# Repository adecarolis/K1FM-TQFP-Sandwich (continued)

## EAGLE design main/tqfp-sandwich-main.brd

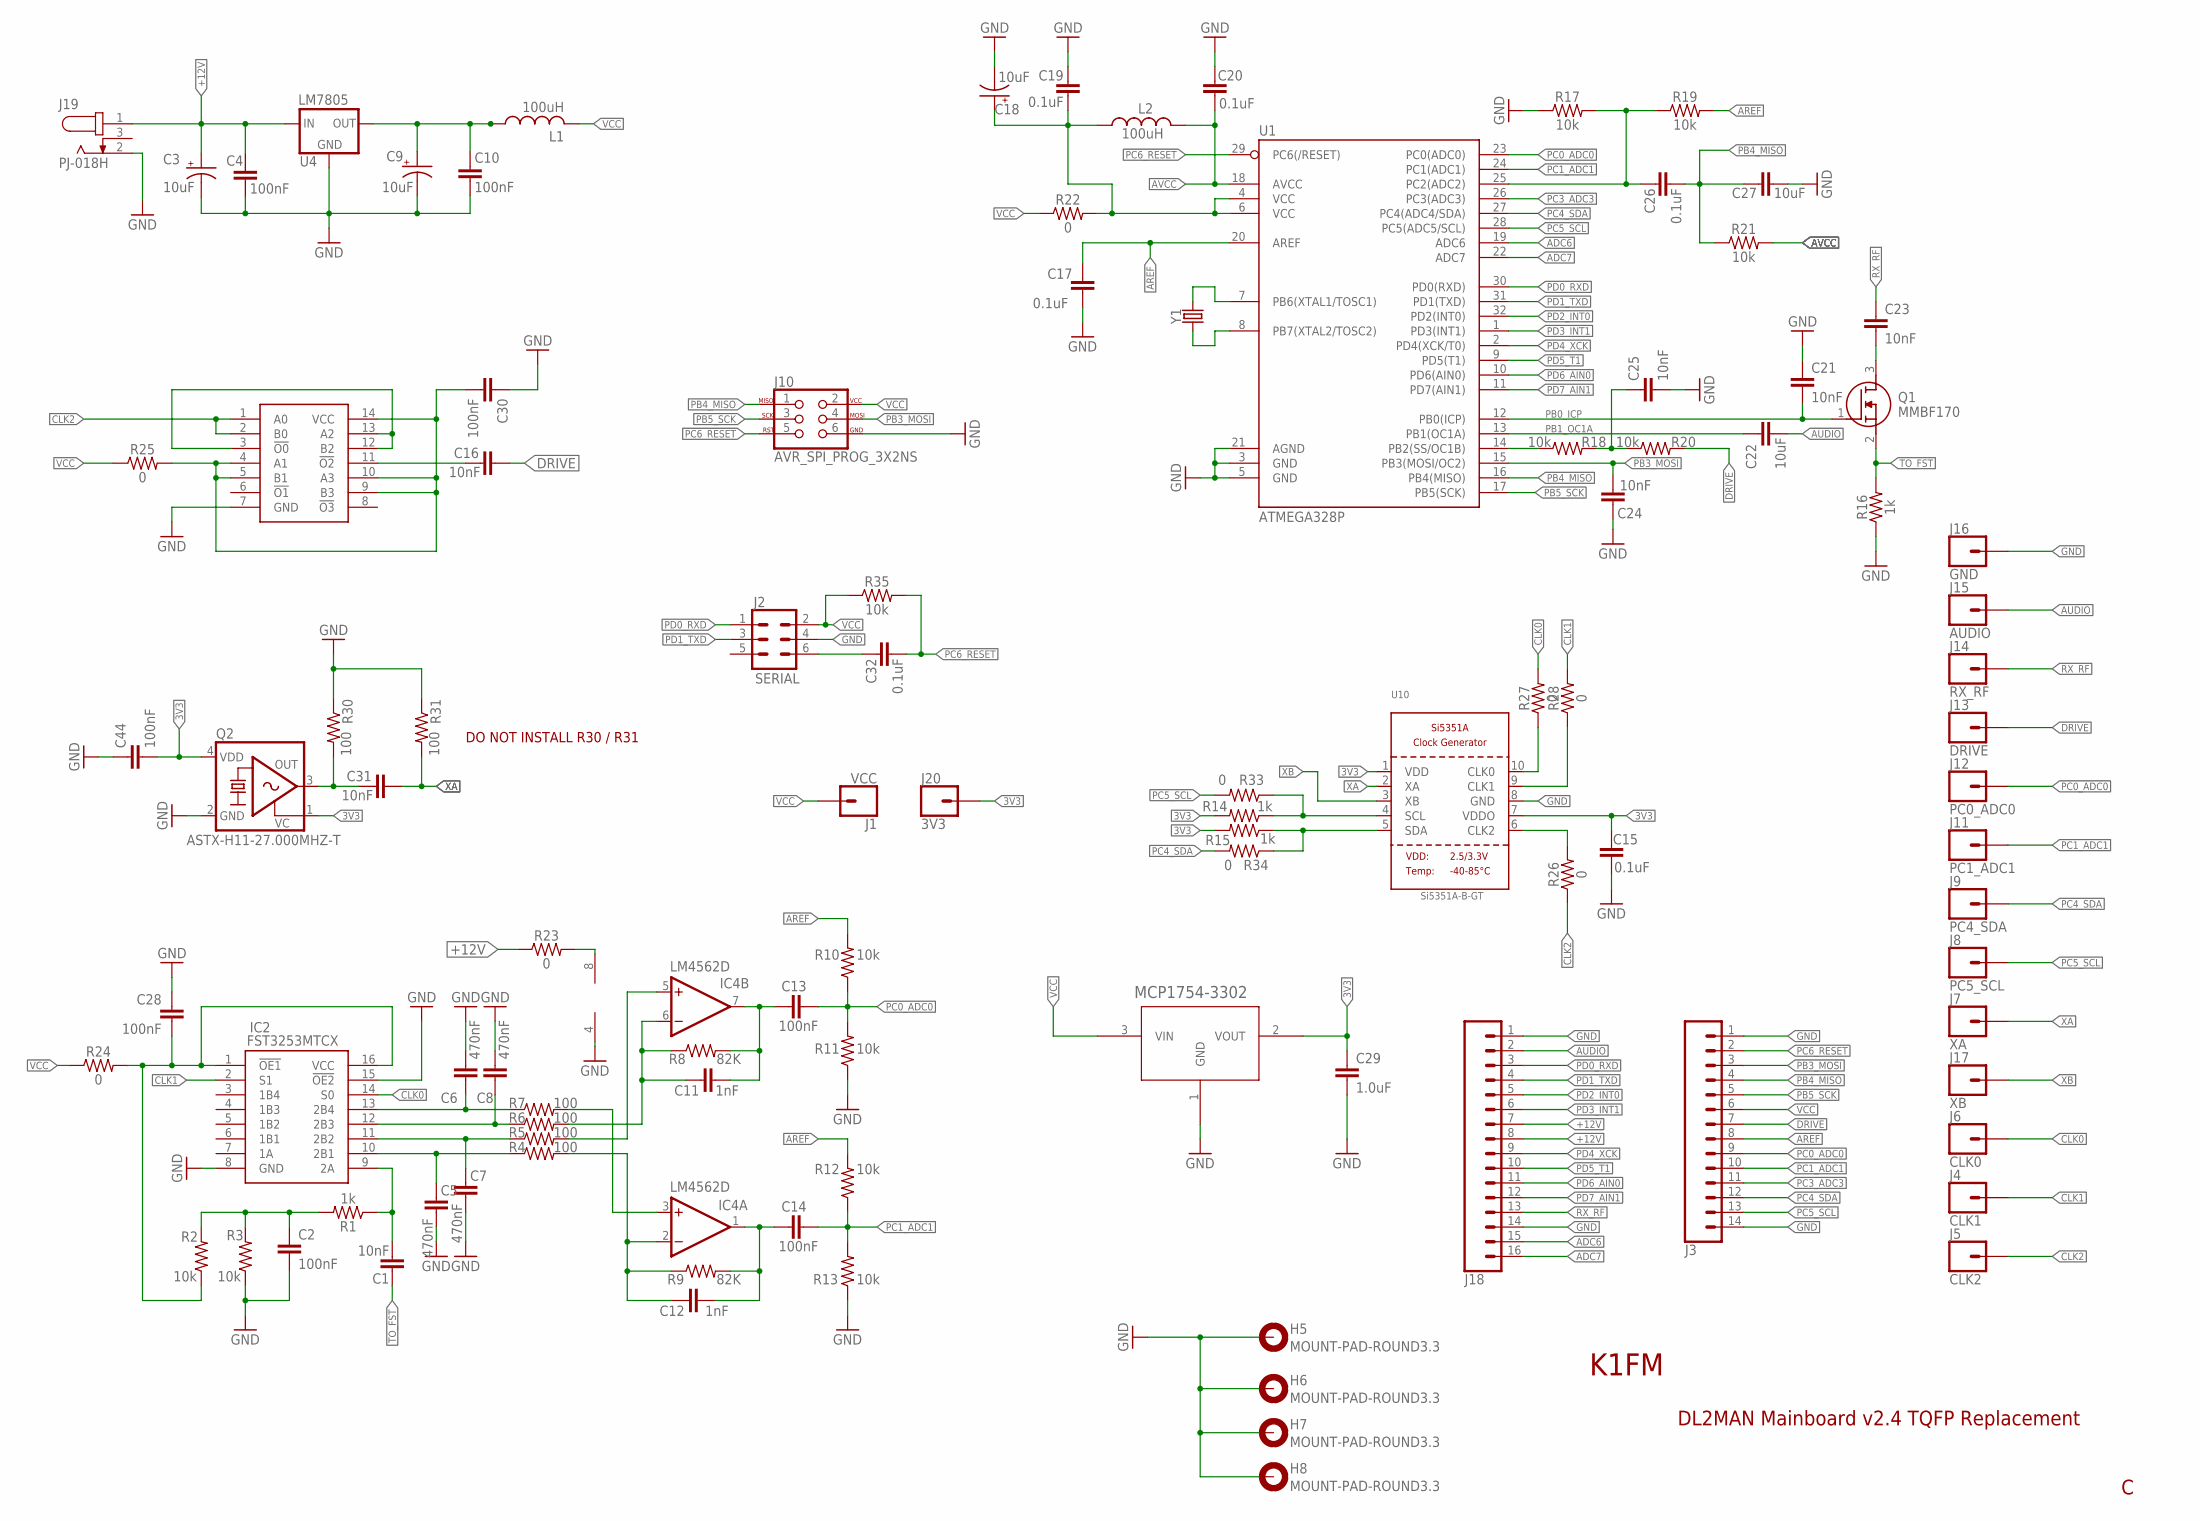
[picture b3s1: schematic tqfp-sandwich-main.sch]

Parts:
C1, C16, C21, C23, C24, C25, C31: 10nF; 0603
C2, C4, C10, C13, C14, C28, C30, C44: 100nF; 0603
C3, C9, C18: 10uF; EIA3216
C5, C6, C7, C8: 470nF; 0603
C11, C12: 1nF; 0603
C15, C17, C19, C20, C26, C32: 0.1uF; 0603
C22, C27: 10uF; 0603
C29: 1.0uF; 0603
H5, H6, H7, H8: MOUNT-PAD-ROUND3.3; 3,3-PAD
IC2: FST3253MTCX; SOP65P640X110-16N
IC3: 74ACT00MTC; SOP65P640X120-14N
IC4: LM4562D; SO08
J1: VCC; 1X01NS_KIT
J2: SERIAL; 2X3
J3: CONN_14; 1X14
J4: CLK1; 1X01_LONGPAD
J5: CLK2; 1X01_LONGPAD
J6: CLK0; 1X01_LONGPAD
J7: XA; 1X01_LONGPAD
J8: PC5_SCL; 1X01_LONGPAD
J9: PC4_SDA; 1X01_LONGPAD
J10: AVR_SPI_PROG_3X2NS; 2X3-NS
J11: PC1_ADC1; 1X01_LONGPAD
J12: PC0_ADC0; 1X01_LONGPAD
J13: DRIVE; 1X01_LONGPAD
J14: RX_RF; 1X01_LONGPAD
J15: AUDIO; 1X01_LONGPAD
J16: GND; 1X01_LONGPAD
J17: XB; 1X01_LONGPAD
J18: CONN_16; 1X16
J19: PJ-018H; CUI_PJ-018H
J20: 3V3; 1X01NS_KIT
L1, L2: 100uH; RESC0805_L
Q1: MMBF170; SOT96P237X111-3N
Q2: ASTX-H11-27.000MHZ-T; 3.2X2.5_KXO-84
R1, R14, R15, R16: 1k; 0603
R2, R3, R10, R11, R12, R13, R17, R18, R19, R20, R21, R35: 10k; 0603
R4, R5, R6, R7, R30, R31: 100; 0603
R8, R9: 82K; 0603
R22, R23, R24, R25, R26, R27, R28, R33, R34: 0; 0603
U1: ATMEGA328P; TQFP32-08
U3: MCP1754X-XXXXX/C; SOT-23A_MC
U4: LM7805; TO-252
U10: Si5351A-B-GT; MSOP10
Y1: CRYSTALSMD-5X3.2-2PAD; CRYSTAL-SMD-5X3.2-2PAD

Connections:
3V3: C15.2, C29.1, C44.2, J20.1, Q2.1 (VC), Q2.4 (VDD), R14.2, R15.2, U3.2 (VOUT), U10.1 (VDD), U10.7 (VDDO)
5V1: C9.+, C10.2, L1.1, U4.2 (OUT)
+12V: C3.+, C4.2, J18.7, J18.8, J19.1, R23.1, U4.1 (IN)
ADC6: J18.15, U1.19 (ADC6)
ADC7: J18.16, U1.22 (ADC7)
AREF: C17.2, J3.8, R10.2, R12.2, R19.2, U1.20 (AREF)
AUDIO: C22.2, J15.1, J18.2
AVCC: C20.1, L2.2, R21.2, U1.18 (AVCC)
CLK0: IC2.14 (S0), J6.1, R27.2
CLK1: IC2.2 (S1), J4.1, R28.2
CLK2: IC3.1 (A0), IC3.2 (B0), J5.1, R26.1
DRIVE: C16.2, J3.7, J13.1, R20.2
GND: C2.2, C3.-, C4.1, C5.2, C6.2, C7.2, C8.2, C9.-, C10.1, C15.1, C17.1, C18.-, C19.2, C20.2, C21.1, C24.1, C25.2, C27.2, C28.1, C29.2, C30.1, C44.1, H5.B3,3, H6.B3,3, H7.B3,3, H8.B3,3, IC2.8 (GND), IC2.15 (!OE2), IC3.7 (GND), IC4.4 (V-), J2.4, J3.1, J3.14, J10.6, J16.1, J18.1, J18.14, J19.2, Q2.2 (GND), R3.1, R11.1, R13.1, R16.1, R17.1, R30.1, R31.1, U1.3 (GND), U1.5 (GND), U1.21 (AGND), U3.1 (GND), U4.3 (GND), U10.8 (GND)
unnamed: U1.7 (PB6(XTAL1/TOSC1)), Y1.P$2 (2)
unnamed: U1.8 (PB7(XTAL2/TOSC2)), Y1.P$1 (1)
unnamed: C23.2, Q1.3 (D)
unnamed: C26.2, R17.2, R19.1, U1.25 (PC2(ADC2))
unnamed: IC3.3 (!O0), IC3.12 (B2), IC3.13 (A2)
unnamed: R18.1, U1.14 (PB2(SS/OC1B))
unnamed: C25.1, R18.2, R20.1
unnamed: C31.1, Q2.3 (OUT), R30.2
unnamed: C5.1, IC2.10 (2B1), R4.1
unnamed: C16.1, IC3.11 (!O2)
unnamed: C18.+, C19.1, L2.1, R22.2, U1.4 (VCC), U1.6 (VCC)
unnamed: C1.2, IC2.9 (2A), R1.1
unnamed: C2.1, R1.2, R2.2, R3.2
unnamed: C7.1, IC2.11 (2B2), R5.1
unnamed: C8.1, IC2.12 (2B3), R6.1
unnamed: C6.1, IC2.13 (2B4), R7.1
unnamed: IC4.5 (+IN), R5.2
unnamed: C12.1, IC4.2 (-IN), R4.2, R9.1
unnamed: C11.1, IC4.6 (-IN), R6.2, R8.1
unnamed: IC4.3 (+IN), R7.2
unnamed: C11.2, C13.1, IC4.7 (OUT), R8.2
unnamed: C12.2, C14.1, IC4.1 (OUT), R9.2
unnamed: IC4.8 (V+), R23.2
unnamed: C28.2, IC2.1 (!OE1), IC2.16 (VCC), R2.1, R24.2
unnamed: C30.2, IC3.4 (A1), IC3.5 (B1), IC3.9 (B3), IC3.10 (A3), IC3.14 (VCC), R25.2
unnamed: R27.1, U10.10 (CLK0)
unnamed: R28.1, U10.9 (CLK1)
unnamed: R26.2, U10.6 (CLK2)
unnamed: R14.1, R33.1, U10.4 (SCL)
unnamed: R15.1, R34.1, U10.5 (SDA)
unnamed: C32.2, J2.6
PB0_ICP: C21.2, Q1.1 (G), U1.12 (PB0(ICP))
PB1_OC1A: C22.1, U1.13 (PB1(OC1A))
PB3_MOSI: C24.2, J3.3, J10.4, U1.15 (PB3(MOSI/OC2))
PB4_MISO: C26.1, C27.1, J3.4, J10.1, R21.1, U1.16 (PB4(MISO))
PB5_SCK: J3.5, J10.3, U1.17 (PB5(SCK))
PC0_ADC0: C13.2, J3.9, J12.1, R10.1, R11.2, U1.23 (PC0(ADC0))
PC1_ADC1: C14.2, J3.10, J11.1, R12.1, R13.2, U1.24 (PC1(ADC1))
PC3_ADC3: J3.11, U1.26 (PC3(ADC3))
PC4_SDA: J3.12, J9.1, R34.2, U1.27 (PC4(ADC4/SDA))
PC5_SCL: J3.13, J8.1, R33.2, U1.28 (PC5(ADC5/SCL))
PC6_RESET: C32.1, J3.2, J10.5, R35.2, U1.29 (PC6(/RESET))
PD0_RXD: J2.1, J18.3, U1.30 (PD0(RXD))
PD1_TXD: J2.3, J18.4, U1.31 (PD1(TXD))
PD2_INT0: J18.5, U1.32 (PD2(INT0))
PD3_INT1: J18.6, U1.1 (PD3(INT1))
PD4_XCK: J18.9, U1.2 (PD4(XCK/T0))
PD5_T1: J18.10, U1.9 (PD5(T1))
PD6_AIN0: J18.11, U1.10 (PD6(AIN0))
PD7_AIN1: J18.12, U1.11 (PD7(AIN1))
RX_RF: C23.1, J14.1, J18.13
TO_FST: C1.1, Q1.2 (S), R16.2
VCC: J1.1, J2.2, J3.6, J10.2, L1.2, R22.1, R24.1, R25.1, R35.1, U3.3 (VIN)
XA: C31.2, J7.1, R31.2, U10.2 (XA)
XB: J17.1, U10.3 (XB)

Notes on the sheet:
DL2MAN Mainboard v2.4 TQFP Replacement
K1FM
DO NOT INSTALL R30 / R31

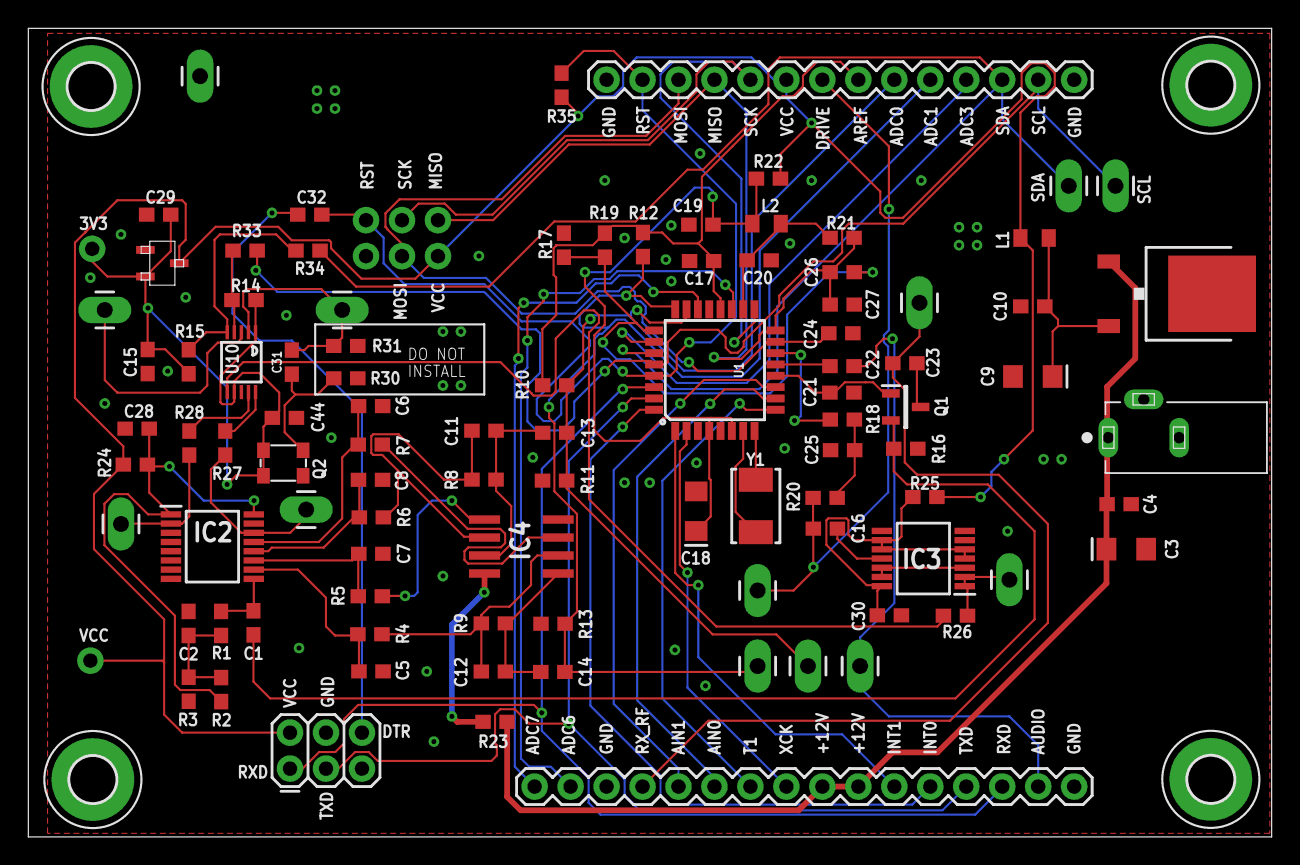
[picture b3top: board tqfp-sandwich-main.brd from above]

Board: 2 copper layers, 87.8 x 57.1 mm, 102 parts (0 on the bottom side), 68 nets.

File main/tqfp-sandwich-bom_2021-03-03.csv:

Qty,Designator,Footprint,Comment,LCSC Part #,Description
5,"C15, C17, C19, C20, C26, C32",C0603,0.1uF,C14663,0.1 uF ceramic capacitors
6,"R4, R5, R6, R7, R30, R31",R0603,100,C22775,100 ohm resistors
8,"C2, C4, C10, C13, C14, C28, C30, C44",C0603,10nF,C57112,10nF ceramic capacitors
2,"L1, L2",RESC0603_L,,C68035,Generic chip inductor
7,"R2, R3, R17, R18, R19, R20, R21, R35",R0603,10k,C98220,10K Resistor
8,"C1, C16, C21, C23, C24, C31, C25, C27, C99",C0603,10nF,C57112,"0.01uF/10nF/10,000pF ceramic capacitors"
1,C22,C0603,10uF,C19702,10uF ceramic capacitors
3,"C3, C9, C18",EIA3216,10uF,C13585,10uF capacitors
4,"R1, R14, R15, R16",R0603,1k,C21190,1k resistors
2,"C11, C12",C0603,1nF,C1588,1nF ceramic capacitors
1,C29,C0603,1uF,C15849,1uF ceramic capacitors
4,"C5, C6, C7, C8",C0603,470nF,C123513,470nF ceramic capacitors
1,IC3,SOP65P640X120-14N,,C133585,"Fairchild Semiconductor 74ACT00MTC, NAND Quad 2 Input NAND, 4.5  5.5 V, 14-Pin TSSOP"
1,Y1,RESONATOR-SMD-1:1,,C112566,20MHz Resonator
2,"R8, R9",R0603,82K,C23254,82K Resistors
1,U1,TQFP32-08,ATMEGA328P_TQFP,C14877,Popular 328P in QFP
1,Q1,SOT96P237X111-3N,,C130879,"MMBF170 N-Channel MOSFET, 500 mA, 60 V, 3-Pin SOT-23 ON Semiconductor"
1,U10,MSOP10,,C529366,Si5351A 8kHz-160MHz I2C Clock Generator
10,"R22, R23, R24, R25, R26, R27, R28, R32, R33, R34",R0603,0,C21189,0 ohm resistor
4,"R10, R11, R12, R13",C0603,10K,C25804,10K Resistor 0.1%
1,U3,SOT-23-5,3.3V LDO,C625392,MCP1754-3302
1,U4,TO-252,12V Regulator,C21706,12V Regulator

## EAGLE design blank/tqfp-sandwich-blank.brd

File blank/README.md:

Blank TQFP Sandwich boards to be used in new project

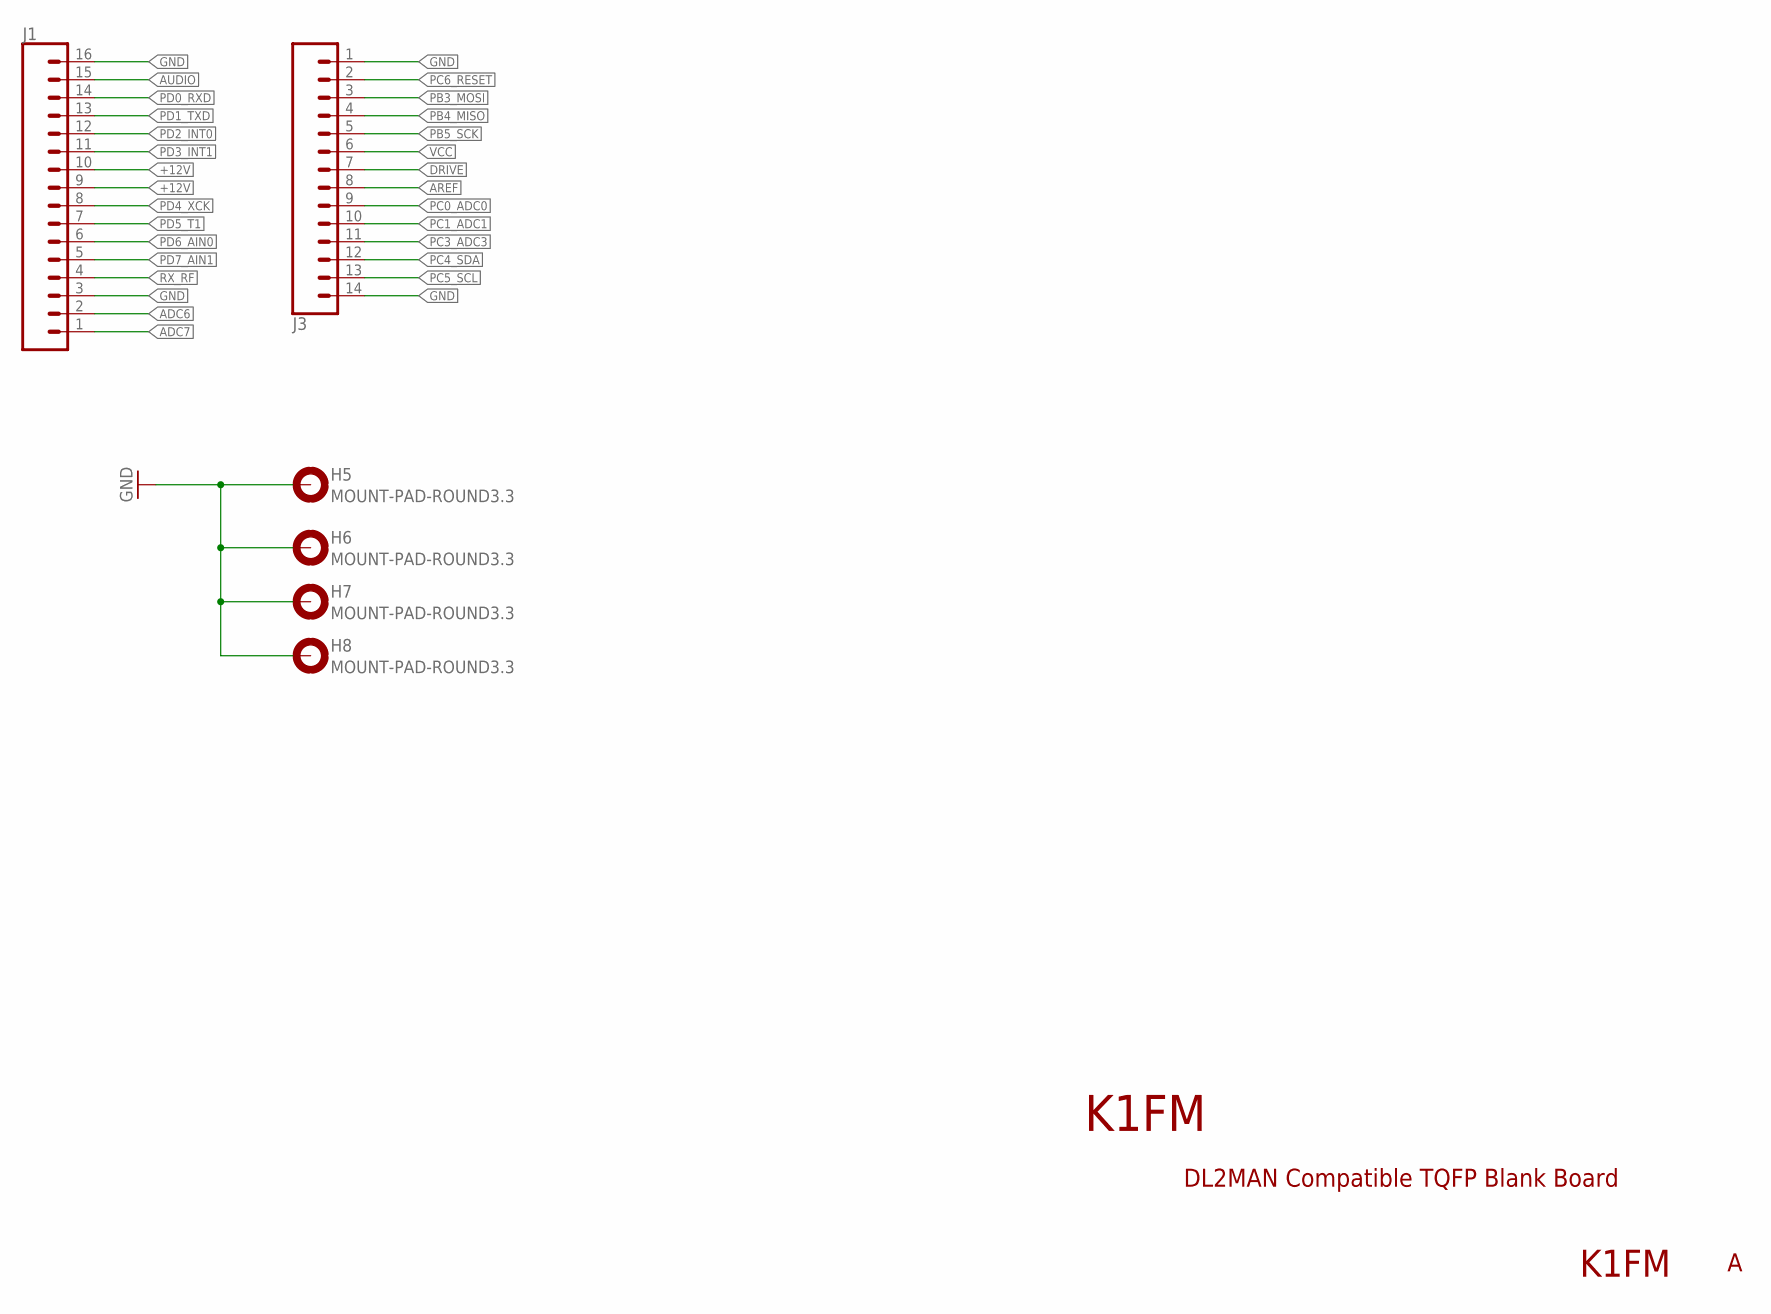
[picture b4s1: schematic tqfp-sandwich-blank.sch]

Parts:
H5, H6, H7, H8: MOUNT-PAD-ROUND3.3; 3,3-PAD
J1: CONN_16; 1X16
J3: CONN_14; 1X14

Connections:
+12V: J1.9, J1.10
ADC6: J1.2
ADC7: J1.1
AREF: J3.8
AUDIO: J1.15
DRIVE: J3.7
GND: H5.B3,3, H6.B3,3, H7.B3,3, H8.B3,3, J1.3, J1.16, J3.1, J3.14
PB3_MOSI: J3.3
PB4_MISO: J3.4
PB5_SCK: J3.5
PC0_ADC0: J3.9
PC1_ADC1: J3.10
PC3_ADC3: J3.11
PC4_SDA: J3.12
PC5_SCL: J3.13
PC6_RESET: J3.2
PD0_RXD: J1.14
PD1_TXD: J1.13
PD2_INT0: J1.12
PD3_INT1: J1.11
PD4_XCK: J1.8
PD5_T1: J1.7
PD6_AIN0: J1.6
PD7_AIN1: J1.5
RX_RF: J1.4
VCC: J3.6

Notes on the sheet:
DL2MAN Compatible TQFP Blank Board
K1FM

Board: 2 copper layers, 6 parts (0 on the bottom side), 2 nets, no tracks yet.

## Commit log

2020-12-24 Add picture
2020-12-24 Fix C18 polarization on the shematic
    BOM Used a non-polarized capacitor, so the comment was changed
2021-03-01 Fix C5 C6 C7 C8 BOM part number / value
2021-03-01 Add source drawings
2021-03-01 Add disclaimer
2021-03-04 Add main, ui, rf, enclosure, blank
2021-03-04 Remove old schematics
2021-03-05 Rename gerber files
2021-03-06 Add capacitor on the MCP6002 power rail
2021-03-08 Remove mosfets, inductors, capacitors values.
    The board can accept two different kind of finals (MMBF170 or IRLML2060).
    Capacitors and inductors need to follow this choice therefore they
    probably shouldn't be explicitly indicated on the schematic.
2021-03-18 GPS fix, Add LM386 (thanks Kris SQ3PCA)
2021-06-10 Removed old gerber file
2021-11-20 Main board BOM corrections (tnx Janez S58J)
